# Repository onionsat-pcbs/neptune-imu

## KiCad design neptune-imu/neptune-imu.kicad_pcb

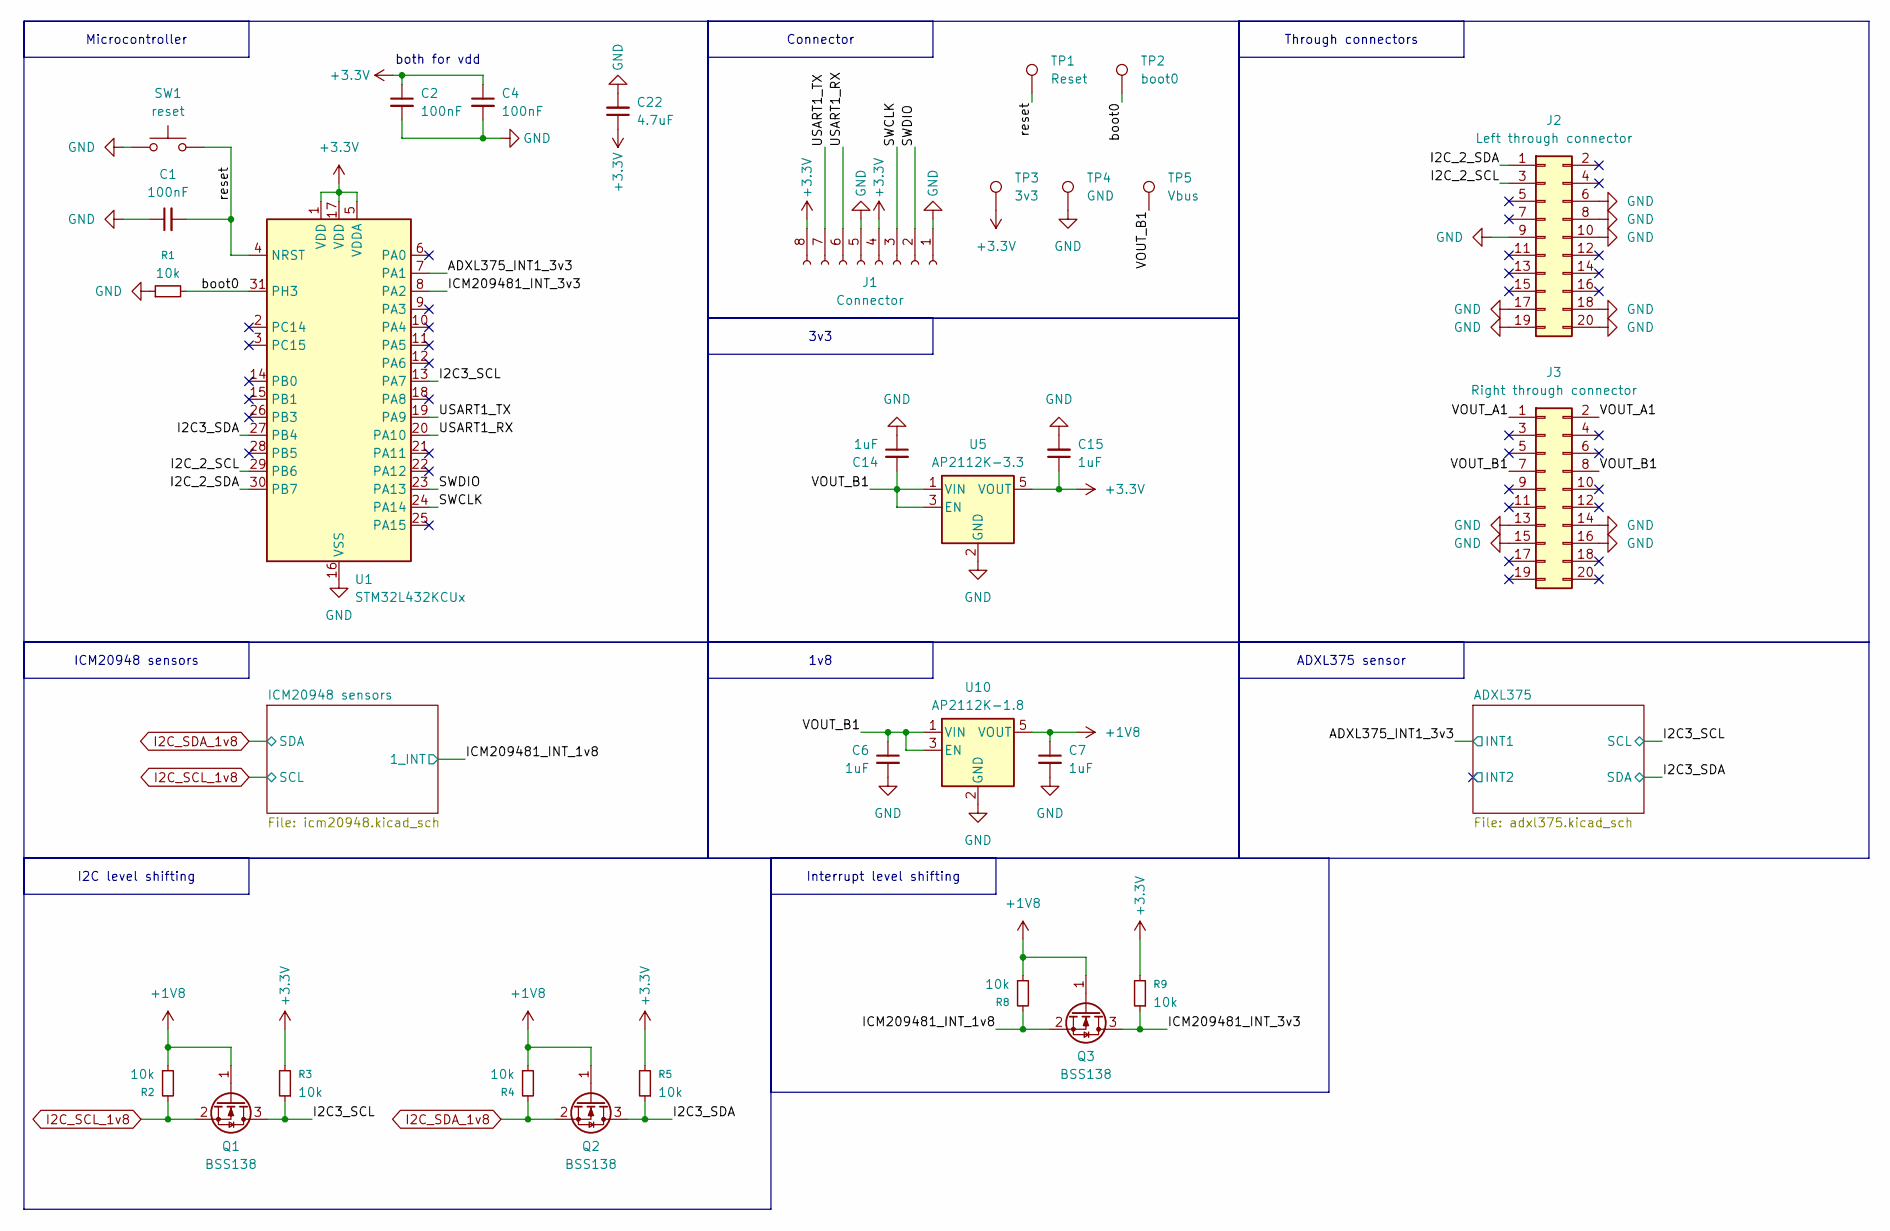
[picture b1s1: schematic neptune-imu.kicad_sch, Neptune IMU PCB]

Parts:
C1: 100nF; C_0603_1608Metric
C2, C4: 100nF; C_0402_1005Metric
C6, C7, C14, C15: 1uF; C_0603_1608Metric
C22: 4.7uF; C_0603_1608Metric
J1: Connector; HDR-SMD_8P-P2.00-H-F-W9.2
J2: Left through connector; gaia_connector
J3: Right through connector; gaia_connector
Q1, Q2, Q3: BSS138; bss138
R1, R2, R3, R4, R5, R8, R9: 10k; R_0402_1005Metric
SW1: reset; KEY-SMD_L4.0-W3.0-LS4.9-1
TP1: Reset; TestPoint_Pad_1.0x1.0mm
TP2: boot0; TestPoint_Pad_1.0x1.0mm
TP3: 3v3; TestPoint_Pad_1.5x1.5mm
TP4: GND; TestPoint_Pad_1.5x1.5mm
TP5: Vbus; TestPoint_Pad_1.5x1.5mm
U1: STM32L432KCUx
U5: AP2112K-3.3; ap2112
U10: AP2112K-1.8; ap2112

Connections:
+1V8: C7.1, Q1.1 (G), Q2.1 (G), Q3.1 (G), R2.1, R4.1, R8.1, U10.5 (VOUT); also elsewhere on the board
+3.3V: C2.1, C4.1, C15.1, C22.1, J1.4, J1.8, R3.2, R5.2, R9.2, TP3.1, U1.1 (VDD), U1.5 (VDDA), U1.17 (VDD), U5.5 (VOUT); also elsewhere on the board
/ADXL375_INT1_3v3: U1.7 (PA1); also elsewhere on the board
/I2C3_SCL: Q1.3 (D), R3.1, U1.13 (PA7); also elsewhere on the board
/I2C3_SDA: Q2.3 (D), R5.1, U1.27 (PB4); also elsewhere on the board
/I2C_2_SCL: J2.3, U1.29 (PB6)
/I2C_2_SDA: J2.1, U1.30 (PB7)
/ICM209481_INT_1v8: Q3.2 (S), R8.2; also elsewhere on the board
/ICM209481_INT_3v3: Q3.3 (D), R9.1, U1.8 (PA2)
/SWCLK: J1.3, U1.24 (PA14)
/SWDIO: J1.2, U1.23 (PA13)
/USART1_RX: J1.6, U1.20 (PA10)
/USART1_TX: J1.7, U1.19 (PA9)
/VOUT_A1: J3.1, J3.2
/VOUT_B1: C6.1, C14.2, J3.7, J3.8, TP5.1, U5.1 (VIN), U5.3 (EN), U10.1 (VIN), U10.3 (EN)
/boot0: R1.2, TP2.1, U1.31 (PH3)
/reset: C1.2, SW1.2, TP1.1, U1.4 (NRST)
GND: C1.1, C2.2, C4.2, C6.2, C7.2, C14.1, C15.2, C22.2, J1.1, J1.5, J2.6, J2.8, J2.9, J2.10, J2.17, J2.18, J2.19, J2.20, J3.13, J3.14, J3.15, J3.16, R1.1, SW1.1, TP4.1, U1.16 (VSS), U1.32 (VSS), U1.33 (VSS), U5.2 (GND), U10.2 (GND); also elsewhere on the board
I2C_SCL_1v8: Q1.2 (S), R2.2; also elsewhere on the board
I2C_SDA_1v8: Q2.2 (S), R4.2; also elsewhere on the board

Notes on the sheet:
both for vdd
3v3
Interrupt level shifting
ADXL375 sensor
Connector
1v8
Microcontroller
ICM20948 sensors
Through connectors
I2C level shifting

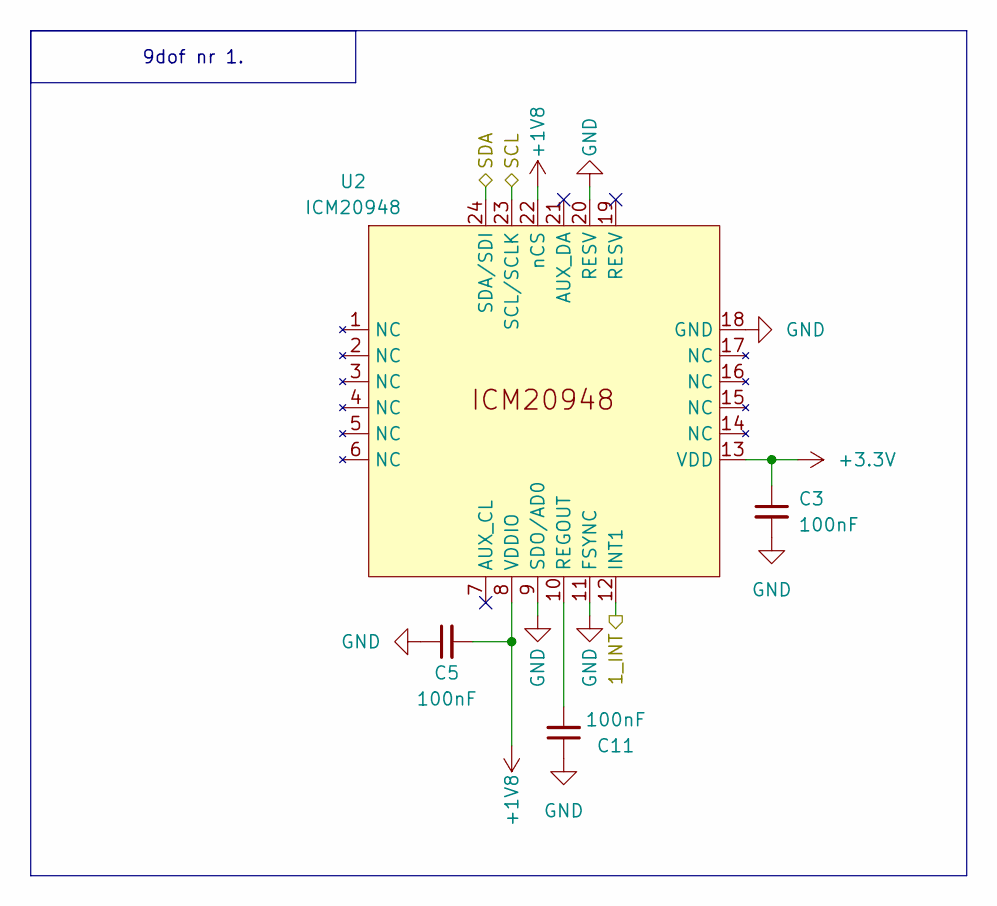
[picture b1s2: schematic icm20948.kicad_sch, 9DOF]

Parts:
C3, C5, C11: 100nF; C_0402_1005Metric
U2: ICM20948; icm20948

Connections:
+1V8: C5.2, U2.8 (VDDIO), U2.22 (nCS); also elsewhere on the board
+3.3V: C3.1, U2.13 (VDD); also elsewhere on the board
/ICM209481_INT_1v8: U2.12 (INT1); also elsewhere on the board
GND: C3.2, C5.1, C11.1, U2.9 (SDO/AD0), U2.11 (FSYNC), U2.18 (GND), U2.20 (RESV); also elsewhere on the board
I2C_SCL_1v8: U2.23 (SCL/SCLK); also elsewhere on the board
I2C_SDA_1v8: U2.24 (SDA/SDI); also elsewhere on the board
unnamed: C11.2, U2.10 (REGOUT)

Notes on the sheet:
9dof nr 1.

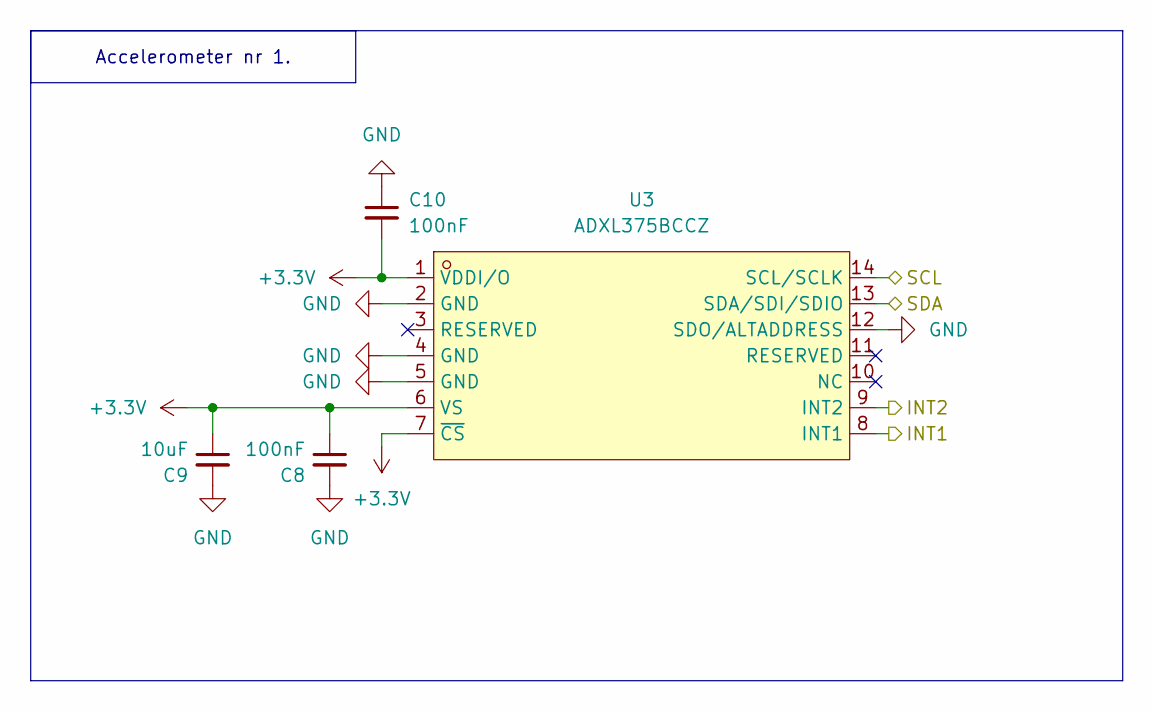
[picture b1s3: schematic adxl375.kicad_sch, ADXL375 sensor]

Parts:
C8, C10: 100nF; C_0402_1005Metric
C9: 10uF; C_0603_1608Metric
U3: ADXL375BCCZ; LGA-14_L5.0-W3.0-P0.80-BL-1; LCSC Part C579466

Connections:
+3.3V: C8.1, C9.1, C10.2, U3.1 (VDDI/O), U3.6 (VS), U3.7 (~CS); also elsewhere on the board
/ADXL375/INT2: U3.9 (INT2)
/ADXL375_INT1_3v3: U3.8 (INT1); also elsewhere on the board
/I2C3_SCL: U3.14 (SCL/SCLK); also elsewhere on the board
/I2C3_SDA: U3.13 (SDA/SDI/SDIO); also elsewhere on the board
GND: C8.2, C9.2, C10.1, U3.2 (GND), U3.4 (GND), U3.5 (GND), U3.12 (SDO/ALTADDRESS); also elsewhere on the board

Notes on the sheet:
Accelerometer nr 1.

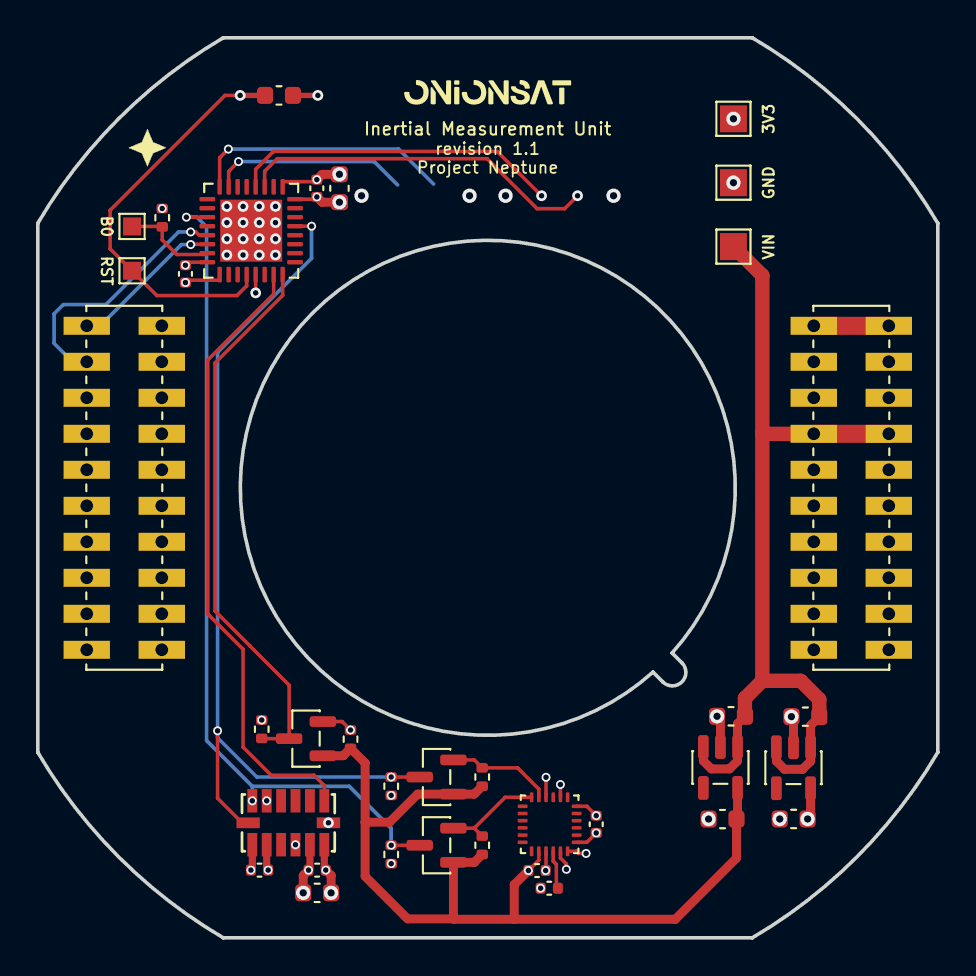
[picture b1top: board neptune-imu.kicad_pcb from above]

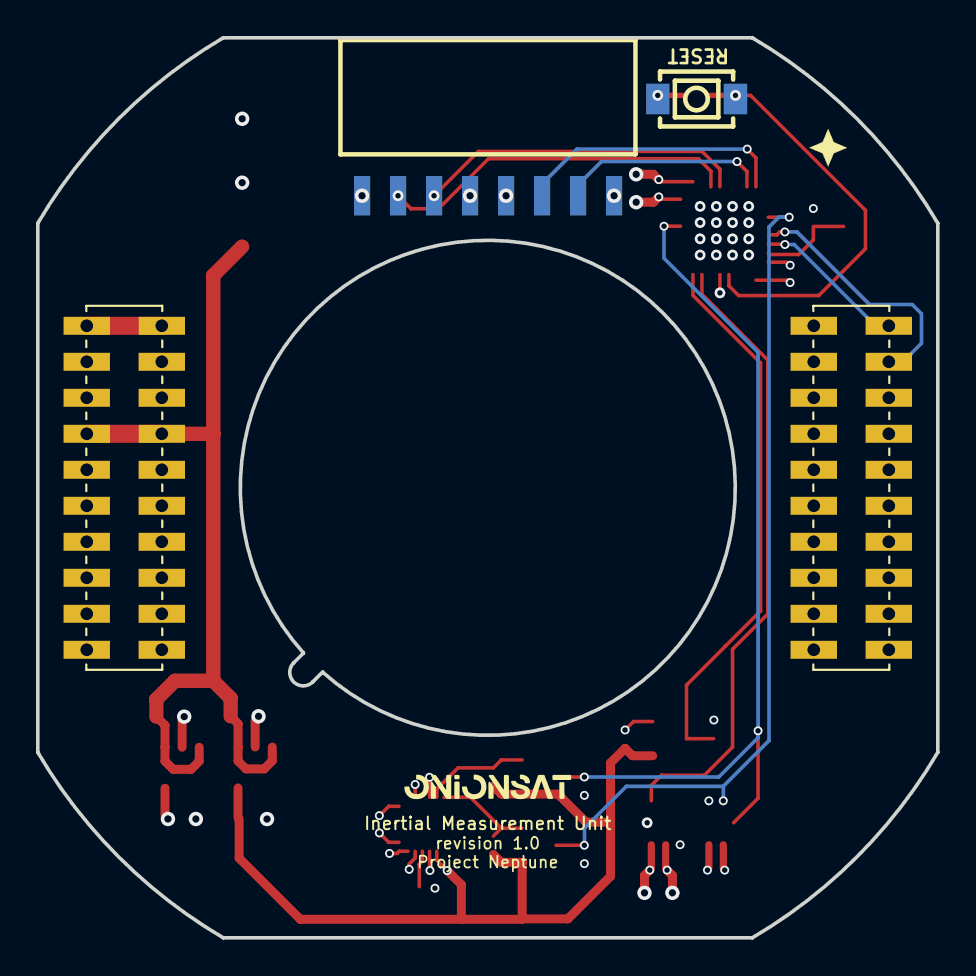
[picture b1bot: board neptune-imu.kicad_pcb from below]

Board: 6 copper layers, 50.0 x 50.0 mm, 38 parts (2 on the bottom side), 21 nets.

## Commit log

2025-12-11 som advancements
2025-12-13 session finished
2025-12-15 Pécsi folytatja a cuccost
2025-12-17 level shifter(bss138) + icm20948 + int lines needed
    Also some final things like star(orientattion)
2025-12-18 going to school
2025-12-19 final
2025-12-19 icm20948 updated for bss138 level shifting
2025-12-21 fixing bugs, production
2026-01-07 fixing 3d models
2026-01-26 v1.1 - PRODUCTION
    Header FIX + Silkscreen FIX
